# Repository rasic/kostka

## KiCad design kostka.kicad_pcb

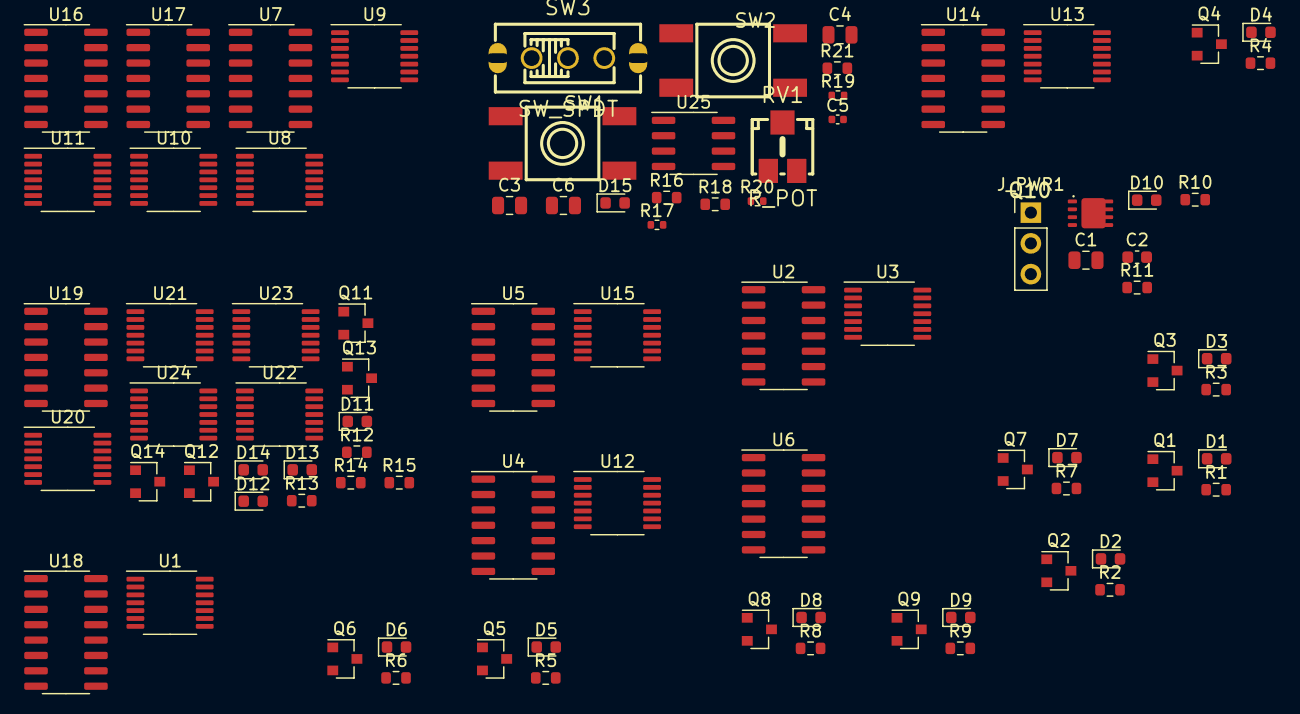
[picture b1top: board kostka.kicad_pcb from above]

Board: 2 copper layers, 86 parts (0 on the bottom side), 112 nets, no tracks yet.

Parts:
C1, C3, C4: 10uF; C_0805_2012Metric
C2: 100nF; C_0603_1608Metric
C5: 10n; C_0402_1005Metric
C6: 47u; C_0805_2012Metric
D1, D2, D3, D4, D5, D6, D7, D8, D9, D11, D12, D13, D14, D15: LED; LED_0603_1608Metric
D10: LED red; LED_0603_1608Metric
J_PWR1: Conn_01x03; PinHeader_1x03_P2.54mm_Vertical
Q1, Q2, Q3, Q4, Q5, Q6, Q7, Q8, Q9, Q11, Q12, Q13, Q14: BC817; SOT-23
Q10: P-MOSFET-MLP_HS; MLP3.3X3.3_HS
R1, R2, R3, R4, R5, R6, R7, R8, R9: 100; R_0603_1608Metric
R10, R12, R13, R14, R15: 220R; R_0603_1608Metric
R11, R16, R18, R21: 10k; R_0603_1608Metric
R17: 220R; R_0402_1005Metric
R19, R20: 10k; R_0402_1005Metric
RV1: R_POT; potentiometer10k
SW1, SW2: SW_MEC_5E; TactileSwitch_C381064
SW3: SW_SPDT; toggleSwitch
U1, U3, U8, U9, U10, U11, U12, U13, U15, U20, U21, U22: 74HC00; TSSOP-14_4.4x5mm_P0.65mm
U2, U4, U5, U6, U14: 74HC32; SOIC-14_3.9x8.7mm_P1.27mm
U7, U16, U17, U19: 74HC08; SOIC-14_3.9x8.7mm_P1.27mm
U18: HEF4518BT; SOIC-16_3.9x9.9mm_P1.27mm
U23, U24: 74HC74; TSSOP-14_4.4x5mm_P0.65mm
U25: LM555xM; SOIC-8_3.9x4.9mm_P1.27mm

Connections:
+5V: C1.1, C2.1, Q10.1, Q10.2, Q10.3, R10.1, R19.1, RV1.1, U1.14, U2.14, U3.14, U4.14, U5.14, U6.14, U7.14, U8.14, U9.14, U10.14, U11.14, U12.14, U13.14, U14.14, U15.14, U16.14, U17.14, U18.16, U19.14, U20.14, U21.14, U22.14, U23.14, U24.14, U25.4, U25.8
/Display Driver/74HC42/D0: U8.1, U8.2, U18.3
/Display Driver/74HC42/D1: U8.4, U8.5, U18.4
/Display Driver/74HC42/D3: U8.9, U8.10, U18.5
/Display Driver/74HC42/D4: U9.12, U9.13, U18.6
/Selection Driver/D0: U19.10, U19.12, U20.1, U20.2, U23.5
/Selection Driver/D1: U19.4, U19.13, U20.4, U20.5, U23.9
/Selection Driver/S0: Q13.1, U19.3, U21.10
/Selection Driver/S1: Q11.1, U19.6, U20.13
/Selection Driver/S2: Q12.1, U19.8, U21.13
/Selection Driver/S3: Q14.1, U19.11
CLK: C4.1, R18.1, SW2.3, SW2.4, U18.1
COUNTER_RST: C3.1, R16.1, SW1.3, SW1.4, U18.7, U22.8, U23.3
GND: C1.2, C2.2, C5.2, C6.2, D1.1, D2.1, D3.1, D4.1, D5.1, D6.1, D7.1, D8.1, D9.1, D10.1, D11.1, D12.1, D13.1, D14.1, J_PWR1.1, J_PWR1.3, R11.2, R16.2, R18.2, R21.2, SW3.3, U1.7, U2.7, U3.7, U4.7, U5.7, U6.7, U7.7, U8.7, U9.7, U10.7, U11.7, U12.7, U13.7, U14.7, U15.7, U16.7, U17.7, U18.8, U19.7, U20.7, U21.7, U22.7, U23.7, U24.7, U25.1
LED1: Q1.1, Q9.1, U2.8
LED2: Q2.1, U4.3
LED3: Q3.1, Q7.1, U14.6
LED4: Q4.1, Q6.1, U1.11
LED5: Q5.1, U5.3
LED8: Q8.1, U6.3
unnamed: C5.1, C6.1, R20.2, U25.2, U25.5, U25.6
unnamed: D1.2, R1.2
unnamed: D2.2, R2.2
unnamed: D3.2, R3.2
unnamed: D4.2, R4.2
unnamed: D5.2, R5.2
unnamed: D6.2, R6.2
unnamed: D7.2, R7.2
unnamed: D8.2, R8.2
unnamed: D9.2, R9.2
unnamed: D10.2, R10.2
unnamed: D11.2, R12.2
unnamed: D12.2, R13.2
unnamed: D13.2, R14.2
unnamed: D14.2, R15.2
unnamed: D15.1, R17.1
unnamed: J_PWR1.2, Q10.5, Q10.6, Q10.7, Q10.8, Q10.9
unnamed: Q1.2, R1.1
unnamed: Q2.2, R2.1
unnamed: Q3.2, R3.1
unnamed: Q4.2, R4.1
unnamed: Q5.2, R5.1
unnamed: Q6.2, R6.1
unnamed: Q7.2, R7.1
unnamed: Q8.2, R8.1
unnamed: Q9.2, R9.1
unnamed: Q10.4, R11.1
unnamed: Q11.2, R12.1
unnamed: Q12.2, R13.1
unnamed: Q13.2, R14.1
unnamed: Q14.2, R15.1
unnamed: R17.2, SW3.2
unnamed: R19.2, R20.1, U25.7
unnamed: R21.1, RV1.3
unnamed: U1.3, U2.2
unnamed: U1.6, U2.1
unnamed: U1.8, U2.5
unnamed: U2.4, U3.11
unnamed: U2.6, U2.9
unnamed: U2.3, U2.10
unnamed: U3.3, U4.2
unnamed: U3.6, U4.1
unnamed: U8.3, U9.1, U9.2, U10.1, U10.9
unnamed: U8.6, U9.4, U9.5, U10.2, U10.5
unnamed: U7.1, U10.3, U16.1, U17.1
unnamed: U9.3, U10.4, U11.12
unnamed: U7.4, U10.6, U16.4, U17.4
unnamed: U10.8, U16.9, U17.9
unnamed: U9.6, U10.10, U11.13
unnamed: U10.11, U11.10
unnamed: U9.11, U10.12, U10.13, U11.2, U11.5
unnamed: U8.8, U9.9, U9.10, U11.1, U11.9
unnamed: U7.2, U7.5, U11.3, U16.10, U16.13
unnamed: U9.8, U11.4
unnamed: U11.6, U16.2, U16.5, U17.10, U17.13
unnamed: U11.8, U17.2, U17.5
unnamed: U11.11, U16.12, U17.12
unnamed: U6.2, U12.3
unnamed: U6.1, U12.6
unnamed: U13.3, U14.2
unnamed: U13.6, U14.1
unnamed: U13.8, U14.10
unnamed: U13.11, U14.9
unnamed: U14.3, U14.5
unnamed: U14.4, U14.8
unnamed: U5.2, U15.3
unnamed: U15.6, U15.9, U15.10
unnamed: U5.1, U15.11
unnamed: U15.8, U15.13
unnamed: U19.1, U19.5, U20.3
unnamed: U19.2, U19.9, U20.6
unnamed: U20.8, U21.12
unnamed: U20.11, U22.2
unnamed: U20.12, U21.6
unnamed: U21.3, U21.9
unnamed: U21.8, U22.1
unnamed: U21.11, U22.10
unnamed: U22.3, U22.4, U22.5
unnamed: U22.6, U22.9
unnamed: U23.2, U23.6, U23.11
unnamed: U23.8, U23.12
Q0: U7.3, U15.2
Q1: U1.2, U7.6
Q2: U13.2, U15.1, U16.8
Q3: U1.1, U13.1, U16.11
Q4: U1.5, U13.5, U15.5, U16.3, U21.1, U21.2
Q5: U1.4, U3.2, U12.2, U13.4, U16.6
Q6: U1.9, U1.10, U3.1, U12.1, U13.9, U13.10, U15.4, U17.8, U21.4, U21.5
Q7: U1.13, U3.5, U3.13, U12.5, U13.13, U17.11
Q8: U1.12, U3.4, U3.12, U12.4, U13.12, U15.12, U17.3, U20.9, U20.10
RAW_CLK: C4.2, D15.2, SW2.1, SW2.2, U25.3
VCC: C3.2, Q1.3, Q2.3, Q3.3, Q4.3, Q5.3, Q6.3, Q7.3, Q8.3, Q9.3, Q11.3, Q12.3, Q13.3, Q14.3, SW1.1, SW1.2, U18.2, U23.1, U23.4, U23.10, U23.13

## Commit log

2020-12-17 Adding .gitignore
2021-01-18 original design realized in Logisim and CrocodileTechnology
2021-02-15 New version
2021-02-15 Add files via upload
    2 to 4 decoder (selection control)
2021-02-16 Version with mode selection
2021-02-16 Dokumentacia WIP
2021-02-16 Adding 555 timer
2021-02-16 Adding LED matrix annotation
2021-02-17 dokumentacia done
2021-02-17 príručka
2021-02-19 Fixed problems with KiCad
